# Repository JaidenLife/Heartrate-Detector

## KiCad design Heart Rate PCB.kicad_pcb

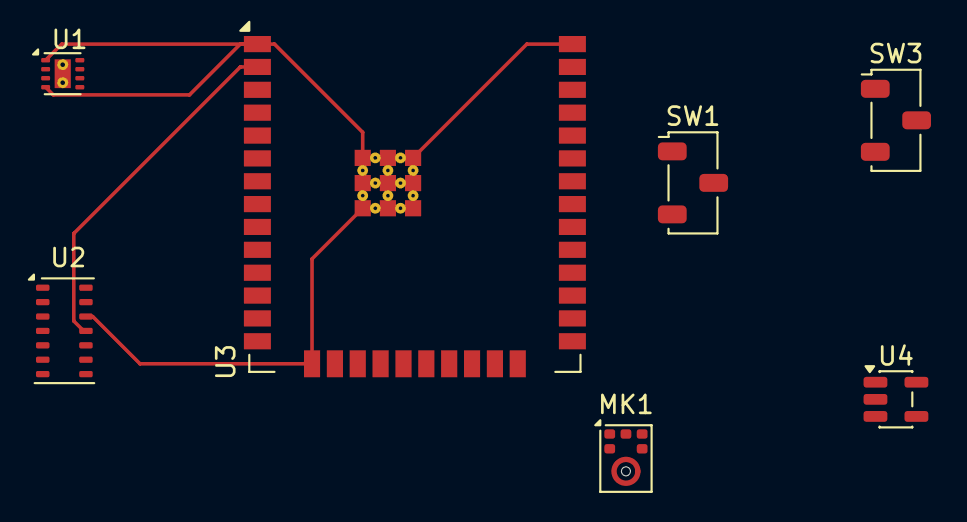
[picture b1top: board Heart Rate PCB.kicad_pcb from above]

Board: 2 copper layers, 7 parts (0 on the bottom side), 11 nets.

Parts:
MK1: SPH0645LM4H; Knowles_SPH0645LM4H-6_3.5x2.65mm
SW1, SW3: SW_Nidec_CAS-120A1; Nidec_Copal_CAS-120A
U1: TPS62172DSG; WSON-8-1EP_2x2mm_P0.5mm_EP0.9x1.6mm_ThermalVias
U2: MAX30102; Maxim_OLGA-14_3.3x5.6mm_P0.8mm
U3: ESP32-WROOM-32E
U4: LT1761-1.8; TSOT-23-5

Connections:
+12V: SW1.1 (C), U1.2 (VIN)
GND: MK1.2 (SEL), MK1.3 (GND), SW1.3 (A), SW3.3 (A), U1.1 (PGND), U1.4 (AGND), U1.5 (FB), U2.4 (PGND), U2.12 (GND), U3.1 (GND), U3.15 (GND), U3.38 (GND), U3.39 (GND), U4.2 (GND)
unnamed: MK1.4 (BCLK), U3.13 (IO14)
unnamed: MK1.6 (DATA), U3.8 (IO32)
unnamed: MK1.5 (VDD), SW3.1 (C), U1.6 (VOS), U2.9 (VLED+), U2.10 (VLED+), U3.2 (VDD), U4.1 (VIN), U4.3 (~SHDN)
unnamed: MK1.1 (WS), U3.23 (IO15)
unnamed: SW1.2 (B), U1.3 (EN)
unnamed: U2.2 (SCL), U3.33 (IO21)
unnamed: U2.3 (SDA), U3.36 (IO22)
unnamed: U2.11 (VDD), U4.4 (BYP), U4.5 (VOUT)
unnamed: U2.13 (~INT), U3.31 (IO19)
